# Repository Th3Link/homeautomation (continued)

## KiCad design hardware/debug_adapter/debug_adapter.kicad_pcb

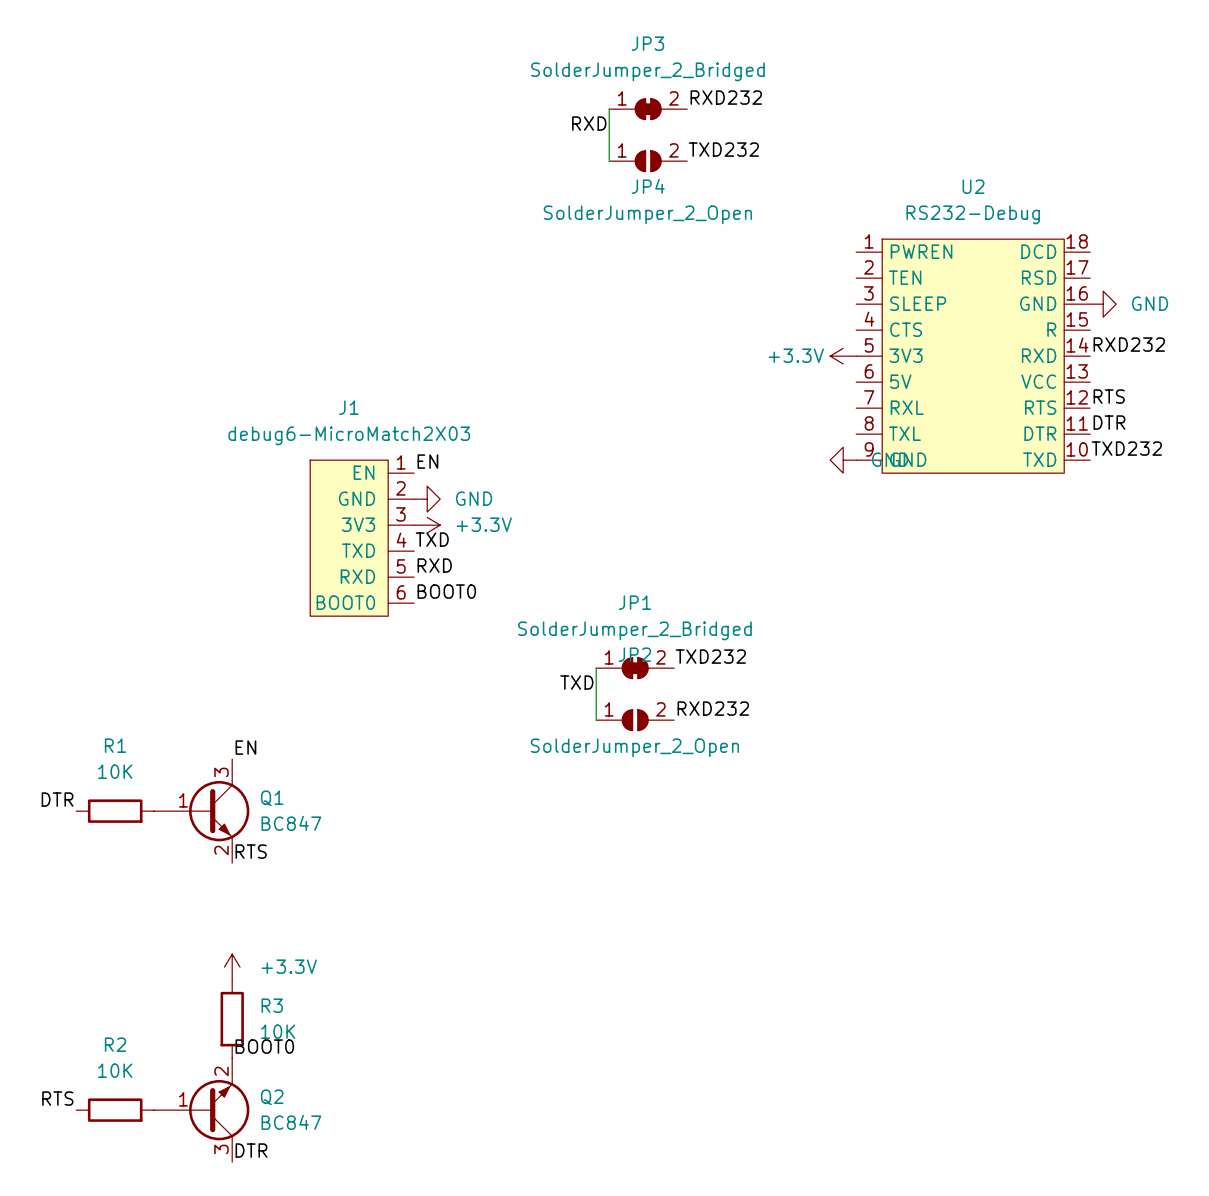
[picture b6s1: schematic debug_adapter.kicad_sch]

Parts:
J1: debug6-MicroMatch2X03; 02x03MicroMatch
JP1, JP3: SolderJumper_2_Bridged; SolderJumper-2_P1.3mm_Bridged_RoundedPad1.0x1.5mm
JP2, JP4: SolderJumper_2_Open; SolderJumper-2_P1.3mm_Open_RoundedPad1.0x1.5mm
Q1, Q2: BC847; SOT-23
R1, R2, R3: 10K; R_0603_1608Metric_Pad0.98x0.95mm_HandSolder
U2: RS232-Debug

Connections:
+3.3V: J1.3 (3V3), R3.1, U2.5 (3V3)
/BOOT0: J1.6 (BOOT0), Q2.2 (E), R3.2
/DTR: Q2.3 (C), R1.1, U2.11 (DTR)
/EN: J1.1 (EN), Q1.3 (C)
/RTS: Q1.2 (E), R2.1, U2.12 (RTS)
/RXD: J1.5 (RXD), JP3.1 (A), JP4.1 (A)
/RXD232: JP2.2 (B), JP3.2 (B), U2.14 (RXD)
/TXD: J1.4 (TXD), JP1.1 (A), JP2.1 (A)
/TXD232: JP1.2 (B), JP4.2 (B), U2.10 (TXD)
GND: J1.2 (GND), U2.9 (GND), U2.16 (GND)
unnamed: Q1.1 (B), R1.2
unnamed: Q2.1 (B), R2.2

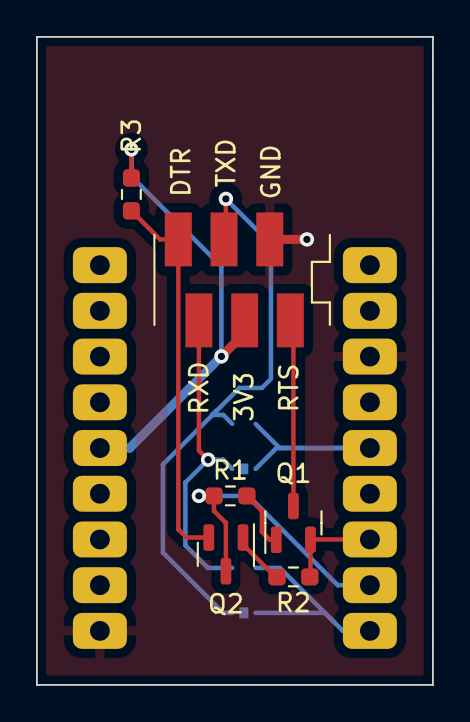
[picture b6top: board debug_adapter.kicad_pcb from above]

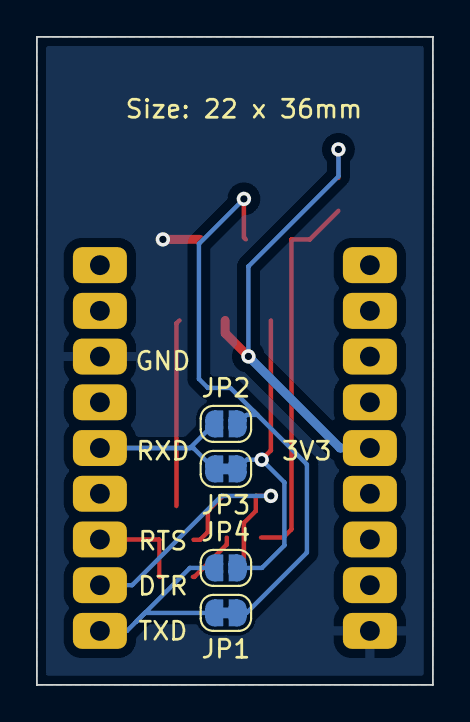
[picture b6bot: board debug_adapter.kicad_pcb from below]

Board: 2 copper layers, 22.0 x 36.0 mm, 11 parts (4 on the bottom side), 12 nets.

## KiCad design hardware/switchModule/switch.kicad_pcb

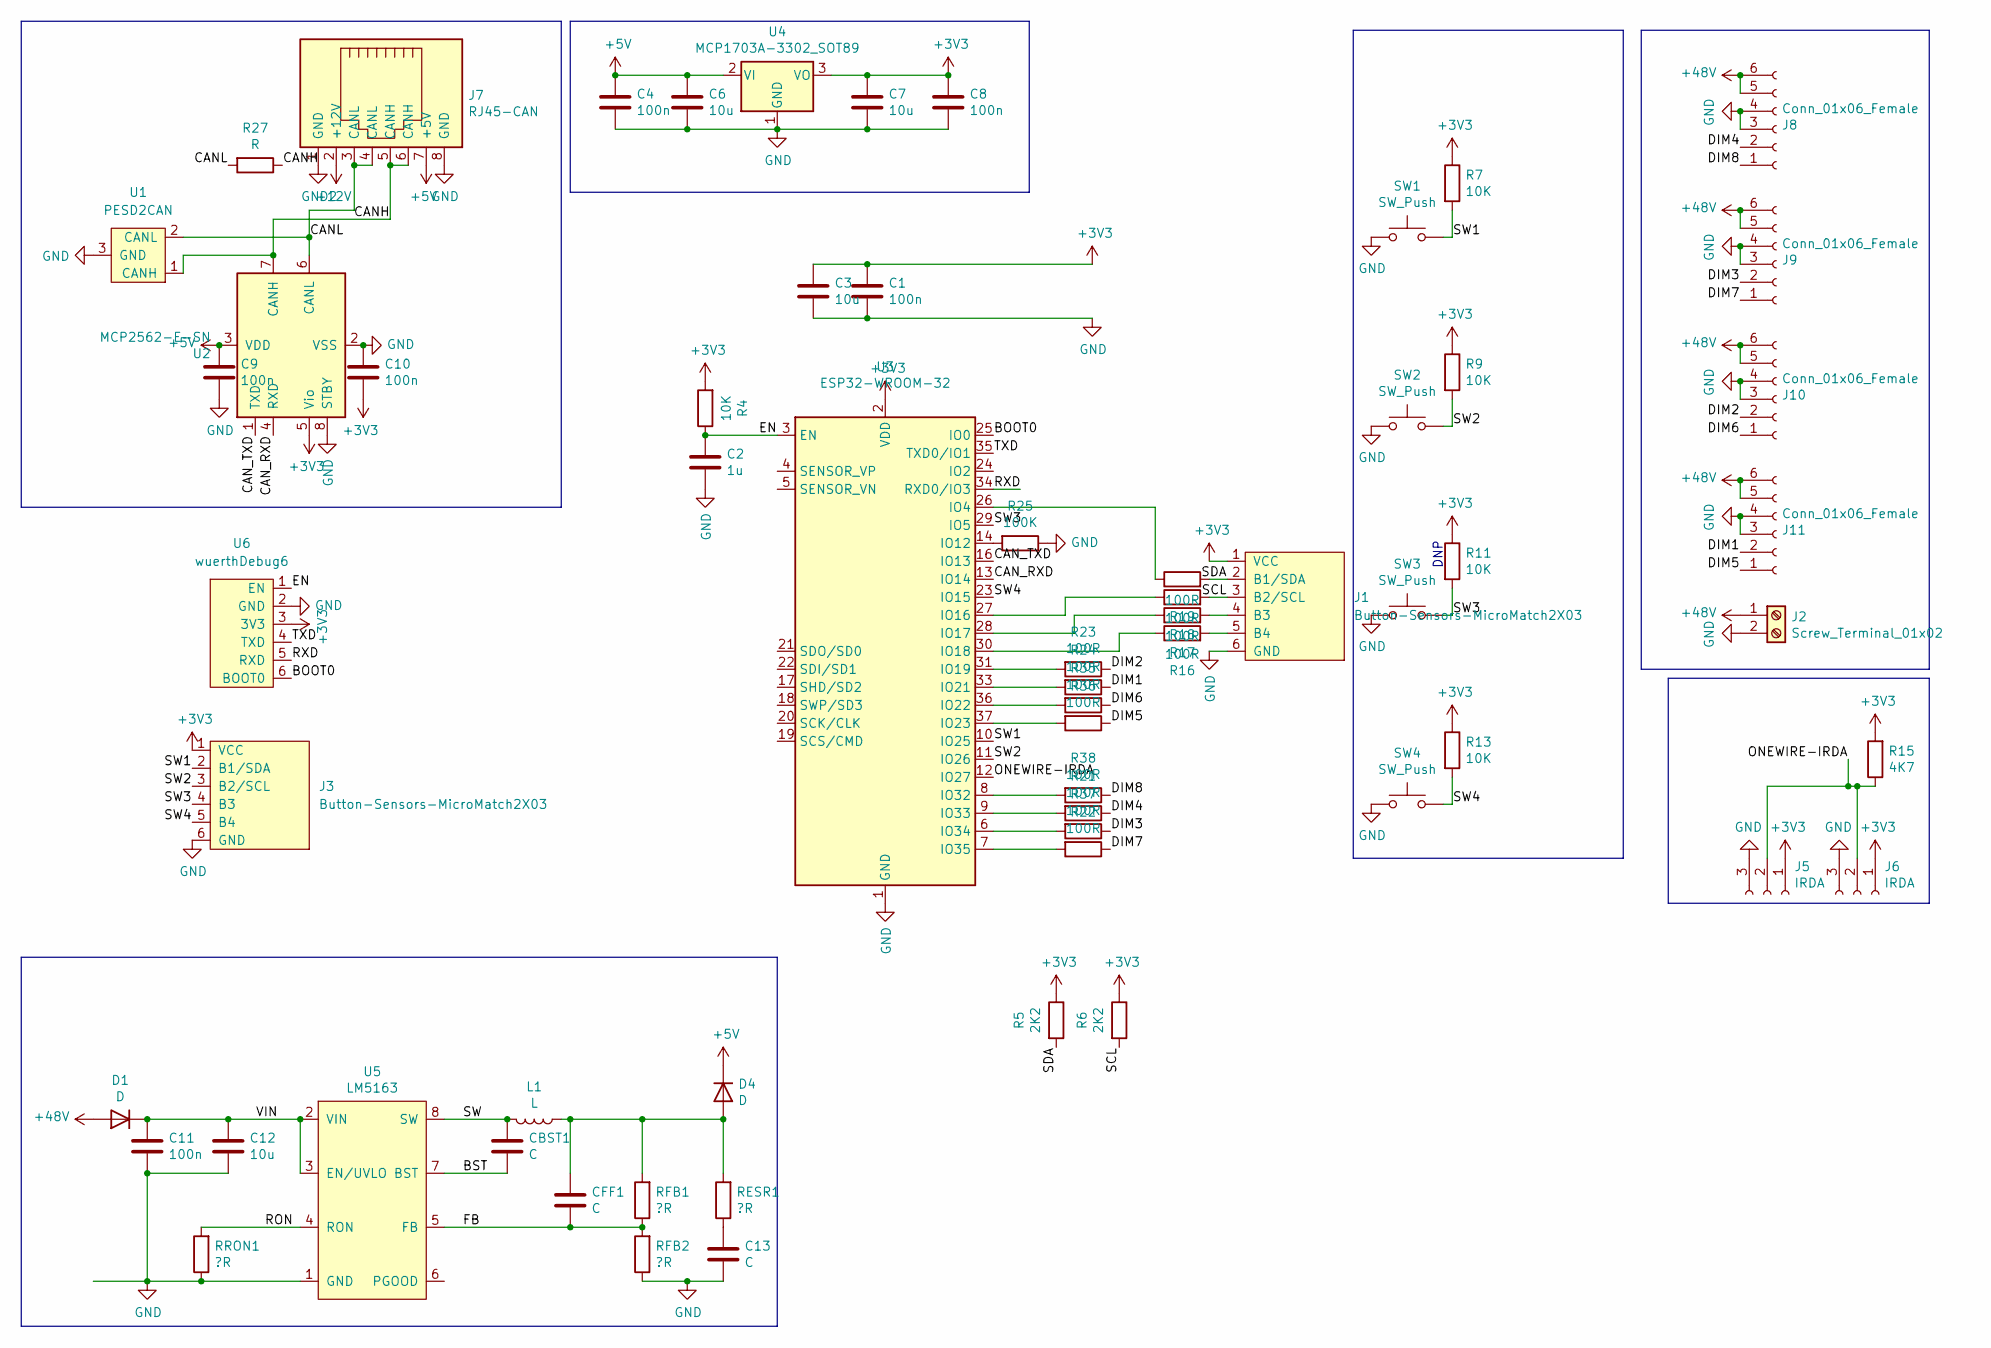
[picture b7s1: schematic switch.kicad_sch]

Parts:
C1, C4, C8, C9, C10, C11: 100n; C_0603_1608Metric_Pad1.08x0.95mm_HandSolder
C2: 1u; C_0603_1608Metric_Pad1.08x0.95mm_HandSolder
C3, C6, C7, C12: 10u; C_0603_1608Metric_Pad1.08x0.95mm_HandSolder
C13: C; C_0603_1608Metric_Pad1.08x0.95mm_HandSolder
CBST1: C; C_0603_1608Metric_Pad1.08x0.95mm_HandSolder
CFF1: C; C_0603_1608Metric_Pad1.08x0.95mm_HandSolder
D1, D4: D; D_SOD-123
J1, J3: Button-Sensors-MicroMatch2X03; 02x03MicroMatch
J2: Screw_Terminal_01x02; TerminalBlock_RND_205-00001_1x02_P5.00mm_Horizontal
J5, J6: IRDA; PinHeader_1x03_P2.54mm_Vertical
J7: RJ45-CAN; RJ45_OST_PJ012-8P8CX_Vertical
J8, J9, J10, J11: Conn_01x06_Female; 02x03MicroMatch
L1: L; L_1210_3225Metric_Pad1.42x2.65mm_HandSolder
R4, R7, R9, R11, R13: 10K; R_0603_1608Metric_Pad0.98x0.95mm_HandSolder
R5, R6: 2K2; R_0603_1608Metric_Pad0.98x0.95mm_HandSolder
R15: 4K7; R_0603_1608Metric_Pad0.98x0.95mm_HandSolder
R16, R17, R18, R19, R21, R22, R23, R24, R35, R36, R37, R38: 100R; R_0603_1608Metric_Pad0.98x0.95mm_HandSolder
R25: 100K; R_0603_1608Metric_Pad0.98x0.95mm_HandSolder
R27: R; R_0603_1608Metric_Pad0.98x0.95mm_HandSolder
RESR1: ?R; R_0603_1608Metric_Pad0.98x0.95mm_HandSolder
RFB1, RFB2: ?R; R_0603_1608Metric_Pad0.98x0.95mm_HandSolder
RRON1: ?R; R_0603_1608Metric_Pad0.98x0.95mm_HandSolder
SW1, SW2, SW3, SW4: SW_Push; SW_SPST_TL3305A
U1: PESD2CAN; SOT-23
U2: MCP2562-E-SN; SOIC-8_3.9x4.9mm_P1.27mm
U3: ESP32-WROOM-32
U4: MCP1703A-3302_SOT89; SOT-89-3_Handsoldering
U5: LM5163; Texas_R-PDSO-G8_EP2.95x4.9mm_Mask2.4x3.1mm_ThermalVias
U6: wuerthDebug6

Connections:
+3V3: C1.1, C3.1, C7.1, C8.1, C10.1, J1.1 (VCC), J3.1 (VCC), J5.1, J6.1, R4.2, R5.1, R6.1, R7.1, R9.1, R11.1, R13.1, R15.2, U2.5 (Vio), U3.2 (VDD), U4.3 (VO), U6.3 (3V3)
+5V: C4.1, C6.1, C9.1, D4.1 (K), J7.7 (+5V), U2.3 (VDD), U4.2 (VI)
+12V: J7.2 (+12V)
+48V: D1.2 (A), J2.1, J8.5, J8.6, J9.5, J9.6, J10.5, J10.6, J11.5, J11.6
/BOOT0: U3.25 (IO0), U6.6 (BOOT0)
/BST: CBST1.2, U5.7 (BST)
/CANH: J7.5 (CANH), J7.6 (CANH), R27.1, U1.1 (CANH), U2.7 (CANH)
/CANL: J7.3 (CANL), J7.4 (CANL), R27.2, U1.2 (CANL), U2.6 (CANL)
/CAN_RXD: U2.4 (RXD), U3.13 (IO14)
/CAN_TXD: U2.1 (TXD), U3.16 (IO13)
/DIM1: J11.2, R24.1
/DIM2: J10.2, R23.1
/DIM3: J9.2, R37.1
/DIM4: J8.2, R21.1
/DIM5: J11.1, R36.1
/DIM6: J10.1, R35.1
/DIM7: J9.1, R22.1
/DIM8: J8.1, R38.1
/EN: C2.1, R4.1, U3.3 (EN), U6.1 (EN)
/FB: CFF1.2, RFB1.1, RFB2.2, U5.5 (FB)
/ONEWIRE-IRDA: J5.2, J6.2, R15.1, U3.12 (IO27)
/RON: RRON1.2, U5.4 (RON)
/RXD: U3.34 (RXD0/IO3), U6.5 (RXD)
/SCL: J1.3 (B2/SCL), R6.2, R18.2
/SDA: J1.2 (B1/SDA), R5.2, R19.2
/SW: CBST1.1, L1.2, U5.8 (SW)
/SW1: J3.2 (B1/SDA), R7.2, SW1.2, U3.10 (IO25)
/SW2: J3.3 (B2/SCL), R9.2, SW2.2, U3.11 (IO26)
/SW3: J3.4 (B3), R11.2, SW3.2, U3.29 (IO5)
/SW4: J3.5 (B4), R13.2, SW4.2, U3.23 (IO15)
/TXD: U3.35 (TXD0/IO1), U6.4 (TXD)
/VIN: C11.1, C12.1, D1.1 (K), U5.2 (VIN), U5.3 (EN/UVLO)
GND: C1.2, C2.2, C3.2, C4.2, C6.2, C7.2, C8.2, C9.2, C10.2, C11.2, C12.2, C13.2, J1.6 (GND), J2.2, J3.6 (GND), J5.3, J6.3, J7.8 (GND), J8.3, J8.4, J9.3, J9.4, J10.3, J10.4, J11.3, J11.4, R25.1, RFB2.1, RRON1.1, SW1.1, SW2.1, SW3.1, SW4.1, U1.3 (GND), U2.2 (VSS), U2.8 (STBY), U3.1 (GND), U3.15 (GND), U3.38 (GND), U3.39 (GND), U4.1 (GND), U5.1 (GND), U6.2 (GND)
GND2: J7.1 (GND)
unnamed: C13.1, RESR1.1
unnamed: CFF1.1, D4.2 (A), L1.1, RESR1.2, RFB1.2
unnamed: J1.4 (B3), R17.2
unnamed: J1.5 (B4), R16.2
unnamed: R16.1, U3.30 (IO18)
unnamed: R17.1, U3.28 (IO17)
unnamed: R18.1, U3.27 (IO16)
unnamed: R19.1, U3.26 (IO4)
unnamed: R21.2, U3.9 (IO33)
unnamed: R22.2, U3.7 (IO35)
unnamed: R23.2, U3.31 (IO19)
unnamed: R24.2, U3.33 (IO21)
unnamed: R25.2, U3.14 (IO12)
unnamed: R35.2, U3.36 (IO22)
unnamed: R36.2, U3.37 (IO23)
unnamed: R37.2, U3.6 (IO34)
unnamed: R38.2, U3.8 (IO32)

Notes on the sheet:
DNP

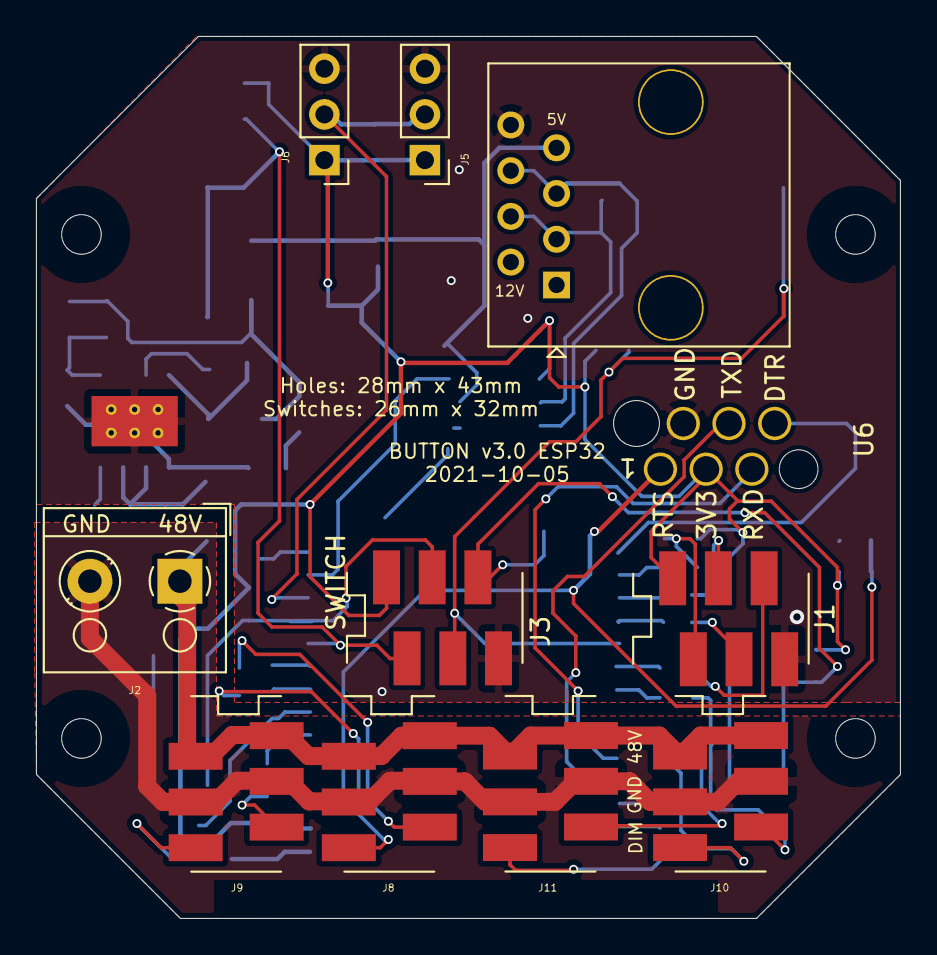
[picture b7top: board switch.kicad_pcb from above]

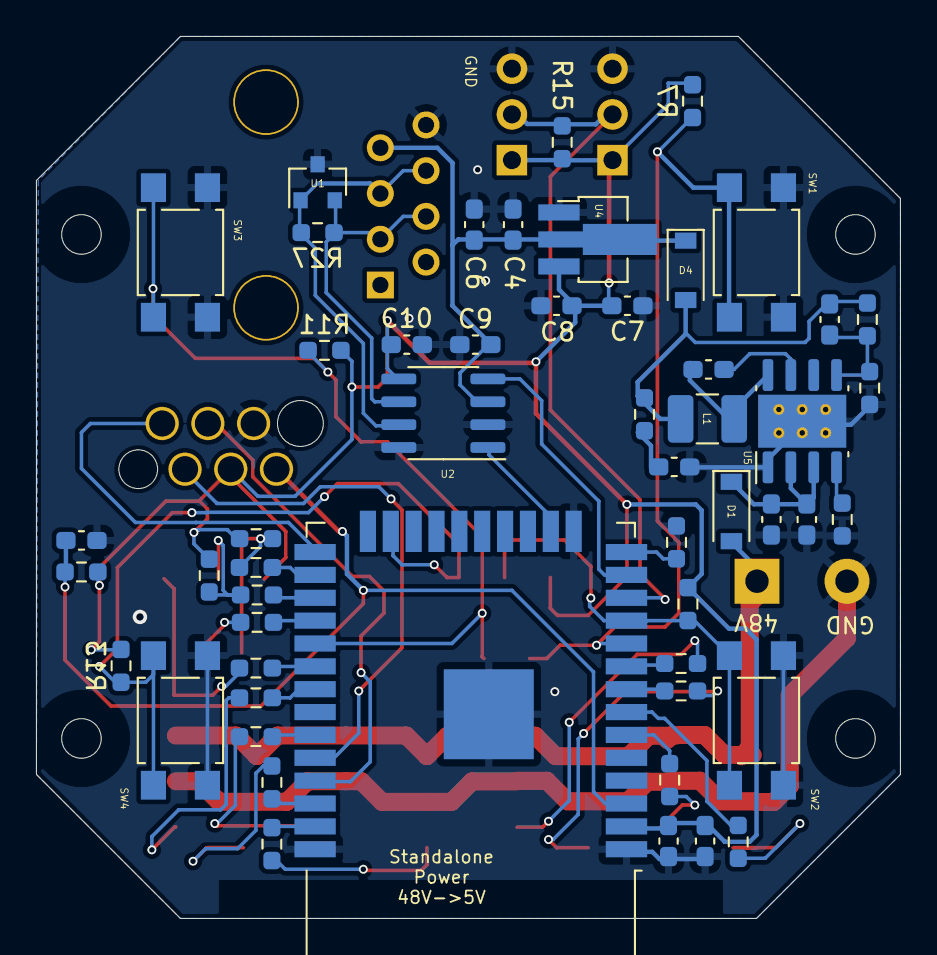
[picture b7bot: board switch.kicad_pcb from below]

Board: 2 copper layers, 48.0 x 49.0 mm, 63 parts (52 on the bottom side), 49 nets.

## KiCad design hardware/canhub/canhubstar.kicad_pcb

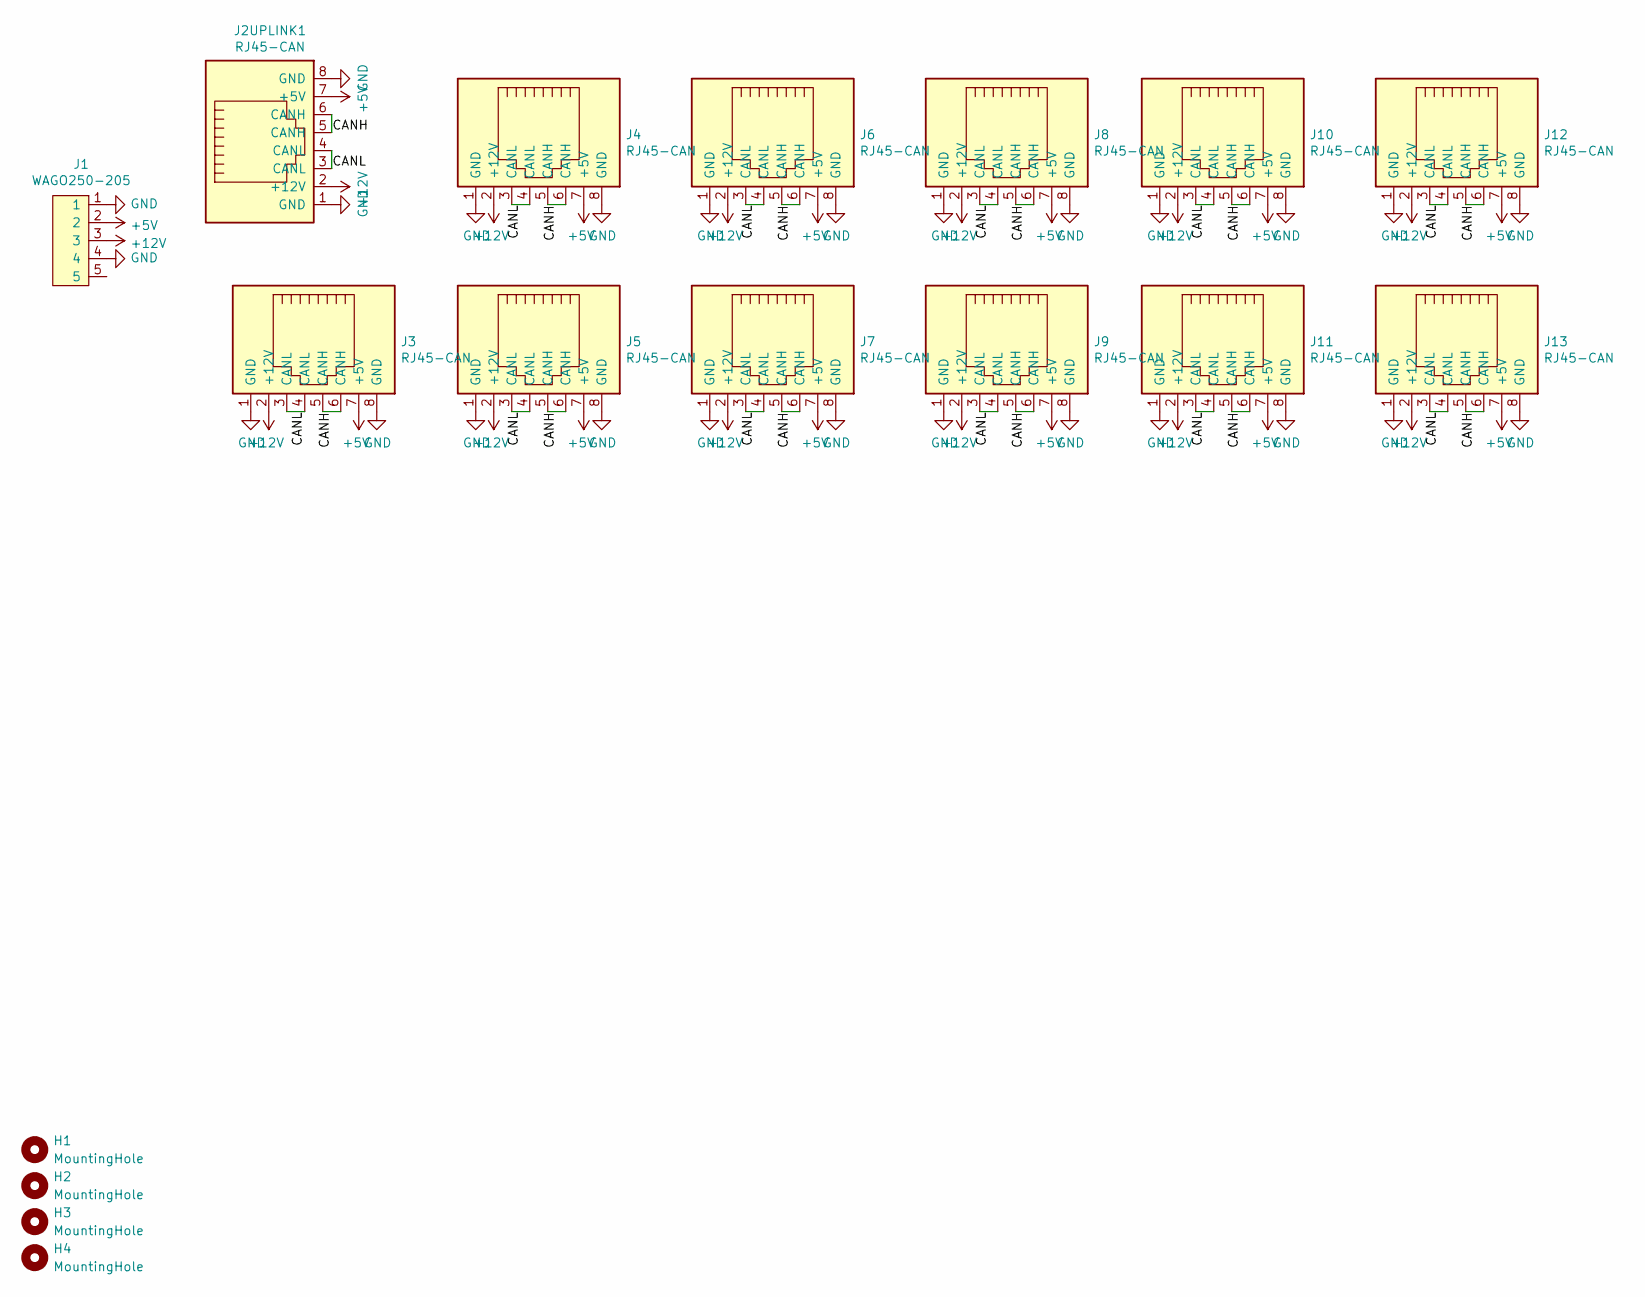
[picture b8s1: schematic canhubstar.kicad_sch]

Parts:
H1, H2, H3, H4: MountingHole; MountingHole_3.2mm_M3
J1: WAGO250-205
J2UPLINK1, J3, J4, J5, J6, J7, J8, J9, J10, J11, J12, J13: RJ45-CAN; RJ45_OST_PJ012-8P8CX_Vertical

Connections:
+5V: J1.2, J2UPLINK1.7 (+5V), J3.7 (+5V), J4.7 (+5V), J5.7 (+5V), J6.7 (+5V), J7.7 (+5V), J8.7 (+5V), J9.7 (+5V), J10.7 (+5V), J11.7 (+5V), J12.7 (+5V), J13.7 (+5V)
+12V: J1.3, J2UPLINK1.2 (+12V), J3.2 (+12V), J4.2 (+12V), J5.2 (+12V), J6.2 (+12V), J7.2 (+12V), J8.2 (+12V), J9.2 (+12V), J10.2 (+12V), J11.2 (+12V), J12.2 (+12V), J13.2 (+12V)
/CANH: J2UPLINK1.5 (CANH), J2UPLINK1.6 (CANH), J3.5 (CANH), J3.6 (CANH), J4.5 (CANH), J4.6 (CANH), J5.5 (CANH), J5.6 (CANH), J6.5 (CANH), J6.6 (CANH), J7.5 (CANH), J7.6 (CANH), J8.5 (CANH), J8.6 (CANH), J9.5 (CANH), J9.6 (CANH), J10.5 (CANH), J10.6 (CANH), J11.5 (CANH), J11.6 (CANH), J12.5 (CANH), J12.6 (CANH), J13.5 (CANH), J13.6 (CANH)
/CANL: J2UPLINK1.3 (CANL), J2UPLINK1.4 (CANL), J3.3 (CANL), J3.4 (CANL), J4.3 (CANL), J4.4 (CANL), J5.3 (CANL), J5.4 (CANL), J6.3 (CANL), J6.4 (CANL), J7.3 (CANL), J7.4 (CANL), J8.3 (CANL), J8.4 (CANL), J9.3 (CANL), J9.4 (CANL), J10.3 (CANL), J10.4 (CANL), J11.3 (CANL), J11.4 (CANL), J12.3 (CANL), J12.4 (CANL), J13.3 (CANL), J13.4 (CANL)
GND: J1.1, J1.4, J2UPLINK1.1 (GND), J2UPLINK1.8 (GND), J3.1 (GND), J3.8 (GND), J4.1 (GND), J4.8 (GND), J5.1 (GND), J5.8 (GND), J6.1 (GND), J6.8 (GND), J7.1 (GND), J7.8 (GND), J8.1 (GND), J8.8 (GND), J9.1 (GND), J9.8 (GND), J10.1 (GND), J10.8 (GND), J11.1 (GND), J11.8 (GND), J12.1 (GND), J12.8 (GND), J13.1 (GND), J13.8 (GND)

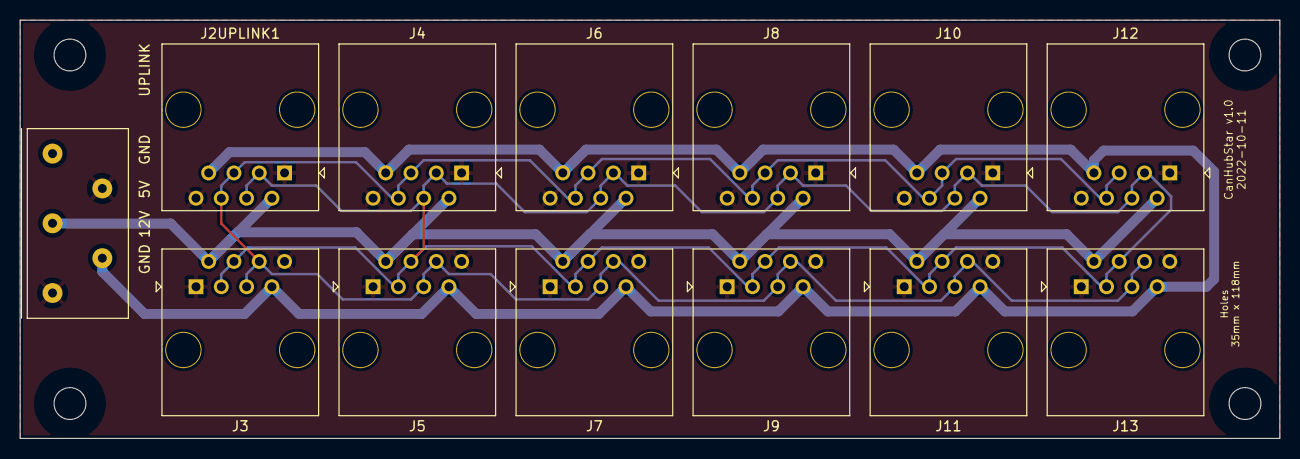
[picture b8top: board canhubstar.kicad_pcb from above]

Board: 2 copper layers, 126.5 x 42.0 mm, 17 parts (0 on the bottom side), 5 nets.
